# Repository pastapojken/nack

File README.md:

# nack
nack keyboard - uses [**QMK**](https://github.com/qmk/qmk_firmware)  
A ISO-friendly, 13x4 keyboard. It has hardware support for basically all the bells and whistles that qmk can provide!

You like my work? Feel free to donate :)  

")

")

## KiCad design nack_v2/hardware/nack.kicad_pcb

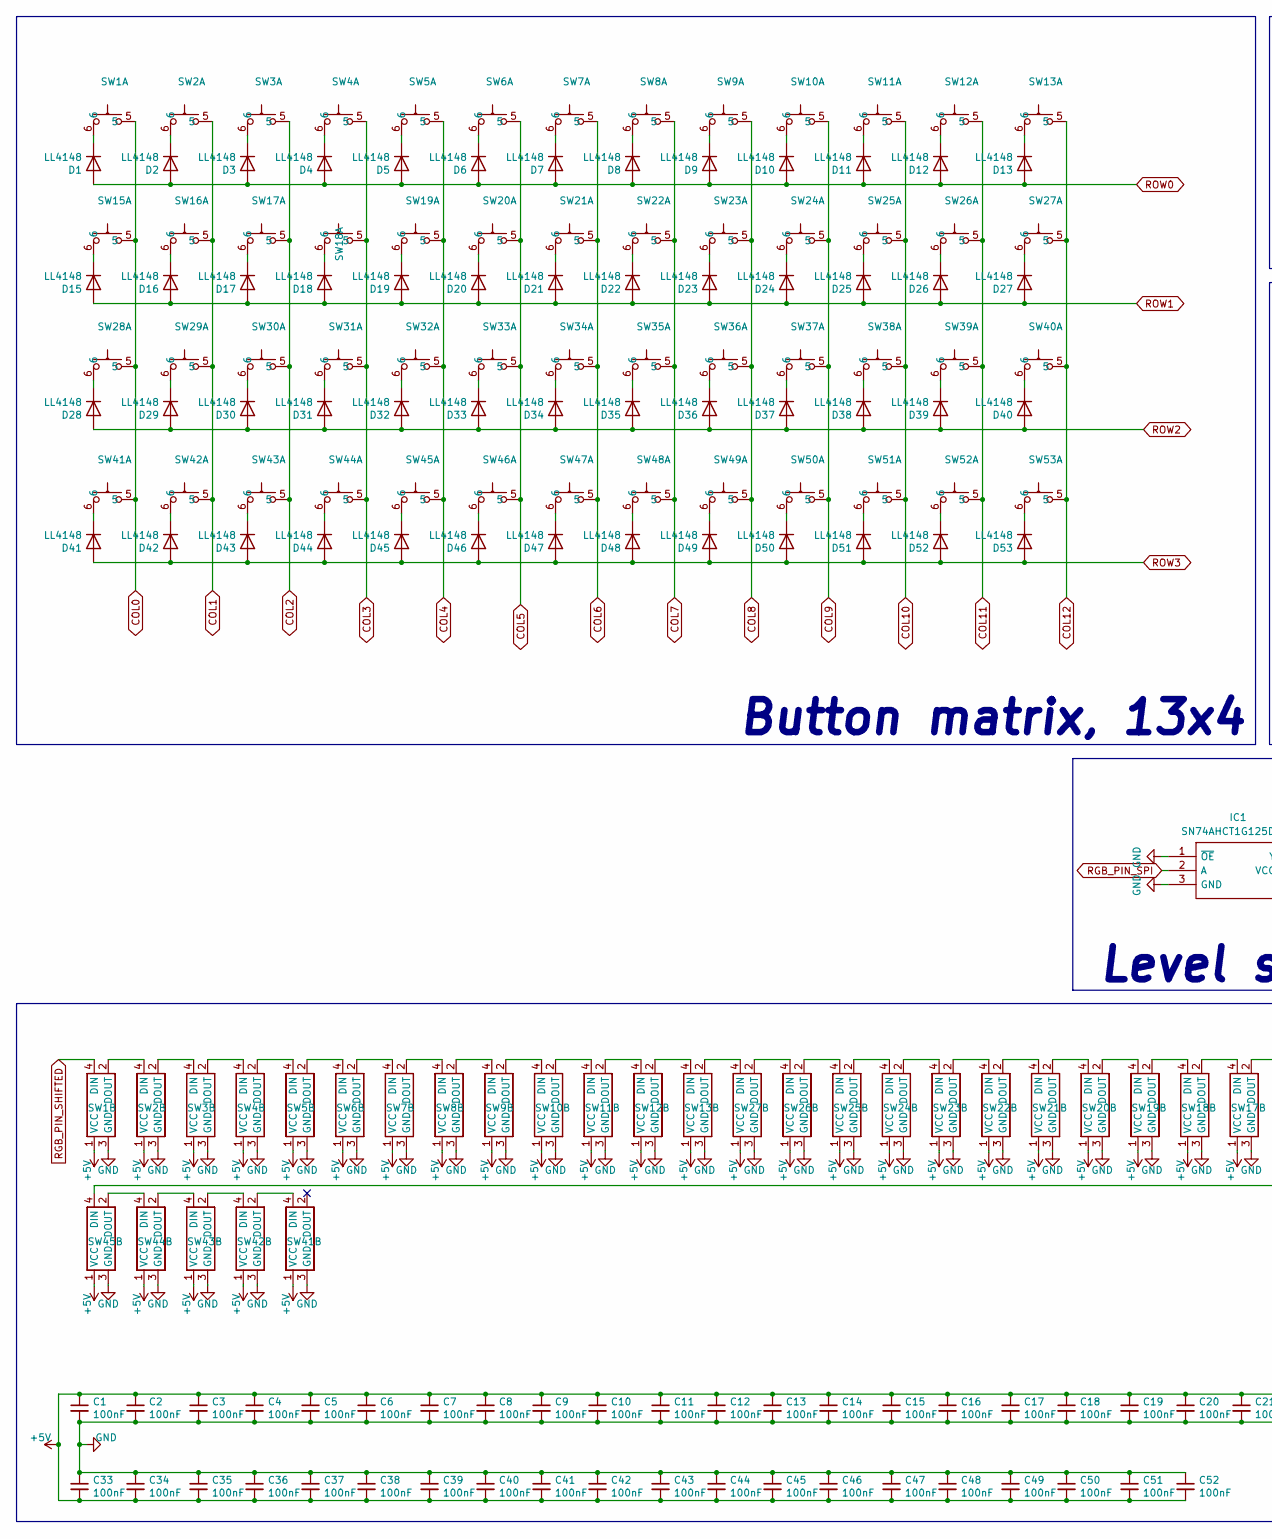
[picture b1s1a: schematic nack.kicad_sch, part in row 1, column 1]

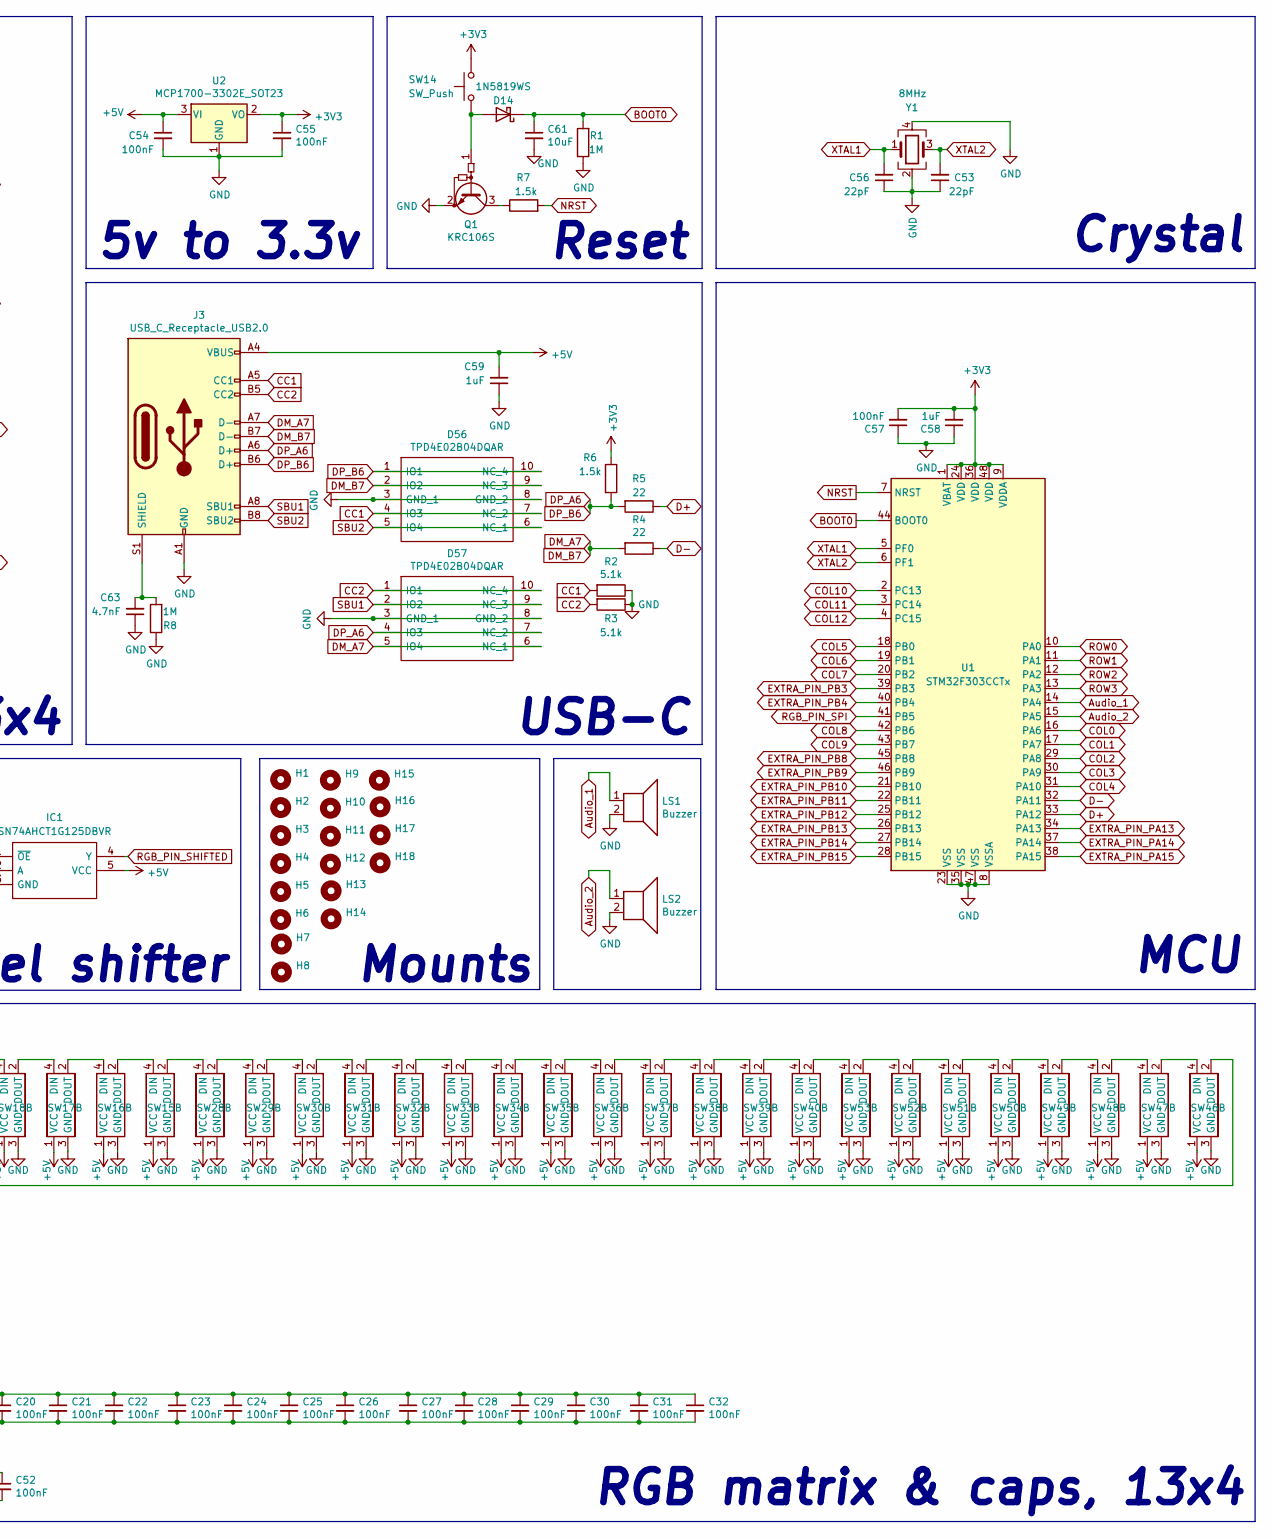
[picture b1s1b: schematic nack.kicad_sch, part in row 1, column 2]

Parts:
C1, C2, C3, C4, C5, C6, C7, C8, C9, C10, C11, C12, C13, C14, C15, C16, C17, C18, C19, C20, C21, C22, C23, C24, C25, C26, C27, C28, C29, C30, C31, C32, C33, C34, C35, C36, C37, C38, C39, C40, C41, C42, C43, C44, C45, C46, C47, C48, C49, C50, C51, C52, C54, C55, C57: 100nF; C_0402_1005Metric
C53, C56: 22pF; C_0402_1005Metric
C58, C59: 1uF; C_0402_1005Metric
C61: 10uF; C_0402_1005Metric
C63: 4.7nF; C_0402_1005Metric
D1, D2, D3, D4, D5, D6, D7, D8, D9, D10, D11, D12, D13, D15, D16, D17, D18, D19, D20, D21, D22, D23, D24, D25, D26, D27, D28, D29, D30, D31, D32, D33, D34, D35, D36, D37, D38, D39, D40, D41, D42, D43, D44, D45, D46, D47, D48, D49, D50, D51, D52, D53: LL4148; D_SOD-123
D14: 1N5819WS; D_SOD-323
D56, D57: TPD4E02B04DQAR; DQA(R-PUSON-N10); Manufacturer_Part_Number TPD4E02B04DQAR; Mouser Part Number 595-TPD4E02B04DQAR
H1, H2, H3, H4, H5, H6, H7, H8, H9, H10, H11, H12, H13, H14, H15, H16, H17, H18: MountingHole; MountingHole_M1.4
IC1: SN74AHCT1G125DBVR; SOT95P280X145-5N; Manufacturer_Part_Number SN74AHCT1G125DBVR; Mouser Part Number 595-SNAHCT1G125DBVR
J3: USB_C_Receptacle_USB2.0; USB_C_Receptacle
LS1, LS2: Buzzer; KLJ-1102
Q1: KRC106S; SOT-23
R1, R8: 1M; R_0402_1005Metric
R2, R3: 5.1k; R_0402_1005Metric
R4, R5: 22; R_0402_1005Metric
R6, R7: 1.5k; R_0402_1005Metric
SW1, SW2, SW3, SW4, SW5, SW6, SW7, SW8, SW9, SW10, SW11, SW12, SW13, SW28, SW29, SW30, SW31, SW32, SW33, SW34, SW35, SW36, SW37, SW38, SW39, SW40: SW_Hotswap_MX; SW_Cherry_MX_Hotswap_RevLED_flipped
SW14: SW_Push; SW_SPST_TL3342
SW15, SW16, SW17, SW18, SW19, SW20, SW21, SW22, SW23, SW24, SW25, SW26, SW27, SW41, SW42, SW43, SW44, SW45, SW46, SW47, SW48, SW49, SW50, SW51, SW52, SW53: SW_Hotswap_MX; SW_Cherry_MX_Hotswap_RevLED
U1: STM32F303CCTx; LQFP-48_7x7mm_P0.5mm; LCSC C81523
U2: MCP1700-3302E_SOT23; SOT-23
Y1: 8MHz; Crystal_SMD_3225-4Pin_3.2x2.5mm; LCSC C253751

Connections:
+3V3: C55.1, C57.2, C58.2, R6.1, SW14.2, U1.1 (VBAT), U1.9 (VDDA), U1.24 (VDD), U1.36 (VDD), U1.48 (VDD), U2.2 (VO)
+5V: C1.1, C2.1, C3.1, C4.1, C5.1, C6.1, C7.1, C8.1, C9.1, C10.1, C11.1, C12.1, C13.1, C14.1, C15.1, C16.1, C17.1, C18.1, C19.1, C20.1, C21.1, C22.1, C23.1, C24.1, C25.1, C26.1, C27.1, C28.1, C29.1, C30.1, C31.1, C32.1, C33.2, C34.2, C35.2, C36.2, C37.2, C38.2, C39.2, C40.2, C41.2, C42.2, C43.2, C44.2, C45.2, C46.2, C47.2, C48.2, C49.2, C50.2, C51.2, C52.2, C54.1, C59.2, IC1.5 (VCC), J3.A4 (VBUS), J3.A9 (VBUS), J3.B4 (VBUS), J3.B9 (VBUS), SW1.1 (VCC), SW2.1 (VCC), SW3.1 (VCC), SW4.1 (VCC), SW5.1 (VCC), SW6.1 (VCC), SW7.1 (VCC), SW8.1 (VCC), SW9.1 (VCC), SW10.1 (VCC), SW11.1 (VCC), SW12.1 (VCC), SW13.1 (VCC), SW15.1 (VCC), SW16.1 (VCC), SW17.1 (VCC), SW18.1 (VCC), SW19.1 (VCC), SW20.1 (VCC), SW21.1 (VCC), SW22.1 (VCC), SW23.1 (VCC), SW24.1 (VCC), SW25.1 (VCC), SW26.1 (VCC), SW27.1 (VCC), SW28.1 (VCC), SW29.1 (VCC), SW30.1 (VCC), SW31.1 (VCC), SW32.1 (VCC), SW33.1 (VCC), SW34.1 (VCC), SW35.1 (VCC), SW36.1 (VCC), SW37.1 (VCC), SW38.1 (VCC), SW39.1 (VCC), SW40.1 (VCC), SW41.1 (VCC), SW42.1 (VCC), SW43.1 (VCC), SW44.1 (VCC), SW45.1 (VCC), SW46.1 (VCC), SW47.1 (VCC), SW48.1 (VCC), SW49.1 (VCC), SW50.1 (VCC), SW51.1 (VCC), SW52.1 (VCC), SW53.1 (VCC), U2.3 (VI)
Audio_1: LS1.1, U1.14 (PA4)
Audio_2: LS2.1, U1.15 (PA5)
BOOT0: C61.1, D14.1 (K), R1.2, U1.44 (BOOT0)
CC1: D56.4 (IO3), D56.7 (NC_2), J3.A5 (CC1), R2.2
CC2: D57.1 (IO1), D57.10 (NC_4), J3.B5 (CC2), R3.2
COL0: SW1.5, SW15.5, SW28.5, SW41.5, U1.16 (PA6)
COL1: SW2.5, SW16.5, SW29.5, SW42.5, U1.17 (PA7)
COL2: SW3.5, SW17.5, SW30.5, SW43.5, U1.29 (PA8)
COL3: SW4.5, SW18.5, SW31.5, SW44.5, U1.30 (PA9)
COL4: SW5.5, SW19.5, SW32.5, SW45.5, U1.31 (PA10)
COL5: SW6.5, SW20.5, SW33.5, SW46.5, U1.18 (PB0)
COL6: SW7.5, SW21.5, SW34.5, SW47.5, U1.19 (PB1)
COL7: SW8.5, SW22.5, SW35.5, SW48.5, U1.20 (PB2)
COL8: SW9.5, SW23.5, SW36.5, SW49.5, U1.42 (PB6)
COL9: SW10.5, SW24.5, SW37.5, SW50.5, U1.43 (PB7)
COL10: SW11.5, SW25.5, SW38.5, SW51.5, U1.2 (PC13)
COL11: SW12.5, SW26.5, SW39.5, SW52.5, U1.3 (PC14)
COL12: SW13.5, SW27.5, SW40.5, SW53.5, U1.4 (PC15)
D+: R5.1, U1.33 (PA12)
D-: R4.1, U1.32 (PA11)
DM_A7: D56.2 (IO2), D56.9 (NC_3), D57.5 (IO4), D57.6 (NC_1), J3.A7 (D-), J3.B7 (D-), R4.2
DP_A6: D56.1 (IO1), D56.10 (NC_4), D57.4 (IO3), D57.7 (NC_2), J3.A6 (D+), J3.B6 (D+), R5.2, R6.2
EXTRA_PIN_PA13: U1.34 (PA13)
EXTRA_PIN_PA14: U1.37 (PA14)
EXTRA_PIN_PA15: U1.38 (PA15)
EXTRA_PIN_PB3: U1.39 (PB3)
EXTRA_PIN_PB4: U1.40 (PB4)
EXTRA_PIN_PB8: U1.45 (PB8)
EXTRA_PIN_PB9: U1.46 (PB9)
EXTRA_PIN_PB10: U1.21 (PB10)
EXTRA_PIN_PB11: U1.22 (PB11)
EXTRA_PIN_PB12: U1.25 (PB12)
EXTRA_PIN_PB13: U1.26 (PB13)
EXTRA_PIN_PB14: U1.27 (PB14)
EXTRA_PIN_PB15: U1.28 (PB15)
GND: C1.2, C2.2, C3.2, C4.2, C5.2, C6.2, C7.2, C8.2, C9.2, C10.2, C11.2, C12.2, C13.2, C14.2, C15.2, C16.2, C17.2, C18.2, C19.2, C20.2, C21.2, C22.2, C23.2, C24.2, C25.2, C26.2, C27.2, C28.2, C29.2, C30.2, C31.2, C32.2, C33.1, C34.1, C35.1, C36.1, C37.1, C38.1, C39.1, C40.1, C41.1, C42.1, C43.1, C44.1, C45.1, C46.1, C47.1, C48.1, C49.1, C50.1, C51.1, C52.1, C53.1, C54.2, C55.2, C56.1, C57.1, C58.1, C59.1, C61.2, C63.1, D56.3 (GND_1), D56.8 (GND_2), D57.3 (GND_1), D57.8 (GND_2), IC1.1 (~OE), IC1.3 (GND), J3.A1 (GND), J3.A12 (GND), J3.B1 (GND), J3.B12 (GND), LS1.2, LS2.2, Q1.2 (E), R1.1, R2.1, R3.1, R8.1, SW1.3 (GND), SW2.3 (GND), SW3.3 (GND), SW4.3 (GND), SW5.3 (GND), SW6.3 (GND), SW7.3 (GND), SW8.3 (GND), SW9.3 (GND), SW10.3 (GND), SW11.3 (GND), SW12.3 (GND), SW13.3 (GND), SW15.3 (GND), SW16.3 (GND), SW17.3 (GND), SW18.3 (GND), SW19.3 (GND), SW20.3 (GND), SW21.3 (GND), SW22.3 (GND), SW23.3 (GND), SW24.3 (GND), SW25.3 (GND), SW26.3 (GND), SW27.3 (GND), SW28.3 (GND), SW29.3 (GND), SW30.3 (GND), SW31.3 (GND), SW32.3 (GND), SW33.3 (GND), SW34.3 (GND), SW35.3 (GND), SW36.3 (GND), SW37.3 (GND), SW38.3 (GND), SW39.3 (GND), SW40.3 (GND), SW41.3 (GND), SW42.3 (GND), SW43.3 (GND), SW44.3 (GND), SW45.3 (GND), SW46.3 (GND), SW47.3 (GND), SW48.3 (GND), SW49.3 (GND), SW50.3 (GND), SW51.3 (GND), SW52.3 (GND), SW53.3 (GND), U1.8 (VSSA), U1.23 (VSS), U1.35 (VSS), U1.47 (VSS), U2.1 (GND), Y1.2, Y1.4
NRST: R7.2, U1.7 (NRST)
unnamed: D1.1 (K), SW1.6
unnamed: D2.1 (K), SW2.6
unnamed: D3.1 (K), SW3.6
unnamed: D4.1 (K), SW4.6
unnamed: D5.1 (K), SW5.6
unnamed: D6.1 (K), SW6.6
unnamed: D7.1 (K), SW7.6
unnamed: D8.1 (K), SW8.6
unnamed: D9.1 (K), SW9.6
unnamed: D10.1 (K), SW10.6
unnamed: D11.1 (K), SW11.6
unnamed: D12.1 (K), SW12.6
unnamed: D13.1 (K), SW13.6
unnamed: D14.2 (A), Q1.1 (B), SW14.1
unnamed: D15.1 (K), SW15.6
unnamed: D16.1 (K), SW16.6
unnamed: D17.1 (K), SW17.6
unnamed: D18.1 (K), SW18.6
unnamed: D19.1 (K), SW19.6
unnamed: D20.1 (K), SW20.6
unnamed: D21.1 (K), SW21.6
unnamed: D22.1 (K), SW22.6
unnamed: D23.1 (K), SW23.6
unnamed: D24.1 (K), SW24.6
unnamed: D25.1 (K), SW25.6
unnamed: D26.1 (K), SW26.6
unnamed: D27.1 (K), SW27.6
unnamed: D28.1 (K), SW28.6
unnamed: D29.1 (K), SW29.6
unnamed: D30.1 (K), SW30.6
unnamed: D31.1 (K), SW31.6
unnamed: D32.1 (K), SW32.6
unnamed: D33.1 (K), SW33.6
unnamed: D34.1 (K), SW34.6
unnamed: D35.1 (K), SW35.6
unnamed: D36.1 (K), SW36.6
unnamed: D37.1 (K), SW37.6
unnamed: D38.1 (K), SW38.6
unnamed: D39.1 (K), SW39.6
unnamed: D40.1 (K), SW40.6
unnamed: D41.1 (K), SW41.6
unnamed: D42.1 (K), SW42.6
unnamed: D43.1 (K), SW43.6
unnamed: D44.1 (K), SW44.6
unnamed: D45.1 (K), SW45.6
unnamed: D46.1 (K), SW46.6
unnamed: D47.1 (K), SW47.6
unnamed: D48.1 (K), SW48.6
unnamed: D49.1 (K), SW49.6
unnamed: D50.1 (K), SW50.6
unnamed: D51.1 (K), SW51.6
unnamed: D52.1 (K), SW52.6
unnamed: D53.1 (K), SW53.6
unnamed: C63.2, J3.S1 (SHIELD), R8.2
unnamed: Q1.3 (C), R7.1
unnamed: SW1.2 (DOUT), SW2.4 (DIN)
unnamed: SW2.2 (DOUT), SW3.4 (DIN)
unnamed: SW3.2 (DOUT), SW4.4 (DIN)
unnamed: SW4.2 (DOUT), SW5.4 (DIN)
unnamed: SW5.2 (DOUT), SW6.4 (DIN)
unnamed: SW6.2 (DOUT), SW7.4 (DIN)
unnamed: SW7.2 (DOUT), SW8.4 (DIN)
unnamed: SW8.2 (DOUT), SW9.4 (DIN)
unnamed: SW9.2 (DOUT), SW10.4 (DIN)
unnamed: SW10.2 (DOUT), SW11.4 (DIN)
unnamed: SW11.2 (DOUT), SW12.4 (DIN)
unnamed: SW12.2 (DOUT), SW13.4 (DIN)
unnamed: SW13.2 (DOUT), SW27.4 (DIN)
unnamed: SW15.4 (DIN), SW16.2 (DOUT)
unnamed: SW15.2 (DOUT), SW28.4 (DIN)
unnamed: SW16.4 (DIN), SW17.2 (DOUT)
unnamed: SW17.4 (DIN), SW18.2 (DOUT)
unnamed: SW18.4 (DIN), SW19.2 (DOUT)
unnamed: SW19.4 (DIN), SW20.2 (DOUT)
unnamed: SW20.4 (DIN), SW21.2 (DOUT)
unnamed: SW21.4 (DIN), SW22.2 (DOUT)
unnamed: SW22.4 (DIN), SW23.2 (DOUT)
unnamed: SW23.4 (DIN), SW24.2 (DOUT)
unnamed: SW24.4 (DIN), SW25.2 (DOUT)
unnamed: SW25.4 (DIN), SW26.2 (DOUT)
unnamed: SW26.4 (DIN), SW27.2 (DOUT)
unnamed: SW28.2 (DOUT), SW29.4 (DIN)
unnamed: SW29.2 (DOUT), SW30.4 (DIN)
unnamed: SW30.2 (DOUT), SW31.4 (DIN)
unnamed: SW31.2 (DOUT), SW32.4 (DIN)
unnamed: SW32.2 (DOUT), SW33.4 (DIN)
unnamed: SW33.2 (DOUT), SW34.4 (DIN)
unnamed: SW34.2 (DOUT), SW35.4 (DIN)
unnamed: SW35.2 (DOUT), SW36.4 (DIN)
unnamed: SW36.2 (DOUT), SW37.4 (DIN)
unnamed: SW37.2 (DOUT), SW38.4 (DIN)
unnamed: SW38.2 (DOUT), SW39.4 (DIN)
unnamed: SW39.2 (DOUT), SW40.4 (DIN)
unnamed: SW40.2 (DOUT), SW53.4 (DIN)
unnamed: SW41.4 (DIN), SW42.2 (DOUT)
unnamed: SW42.4 (DIN), SW43.2 (DOUT)
unnamed: SW43.4 (DIN), SW44.2 (DOUT)
unnamed: SW44.4 (DIN), SW45.2 (DOUT)
unnamed: SW45.4 (DIN), SW46.2 (DOUT)
unnamed: SW46.4 (DIN), SW47.2 (DOUT)
unnamed: SW47.4 (DIN), SW48.2 (DOUT)
unnamed: SW48.4 (DIN), SW49.2 (DOUT)
unnamed: SW49.4 (DIN), SW50.2 (DOUT)
unnamed: SW50.4 (DIN), SW51.2 (DOUT)
unnamed: SW51.4 (DIN), SW52.2 (DOUT)
unnamed: SW52.4 (DIN), SW53.2 (DOUT)
RGB_PIN_SHIFTED: IC1.4 (Y), SW1.4 (DIN)
RGB_PIN_SPI: IC1.2 (A), U1.41 (PB5)
ROW0: D1.2 (A), D2.2 (A), D3.2 (A), D4.2 (A), D5.2 (A), D6.2 (A), D7.2 (A), D8.2 (A), D9.2 (A), D10.2 (A), D11.2 (A), D12.2 (A), D13.2 (A), U1.10 (PA0)
ROW1: D15.2 (A), D16.2 (A), D17.2 (A), D18.2 (A), D19.2 (A), D20.2 (A), D21.2 (A), D22.2 (A), D23.2 (A), D24.2 (A), D25.2 (A), D26.2 (A), D27.2 (A), U1.11 (PA1)
ROW2: D28.2 (A), D29.2 (A), D30.2 (A), D31.2 (A), D32.2 (A), D33.2 (A), D34.2 (A), D35.2 (A), D36.2 (A), D37.2 (A), D38.2 (A), D39.2 (A), D40.2 (A), U1.12 (PA2)
ROW3: D41.2 (A), D42.2 (A), D43.2 (A), D44.2 (A), D45.2 (A), D46.2 (A), D47.2 (A), D48.2 (A), D49.2 (A), D50.2 (A), D51.2 (A), D52.2 (A), D53.2 (A), U1.13 (PA3)
SBU1: D57.2 (IO2), D57.9 (NC_3), J3.A8 (SBU1)
SBU2: D56.5 (IO4), D56.6 (NC_1), J3.B8 (SBU2)
XTAL1: C56.2, U1.5 (PF0), Y1.1
XTAL2: C53.2, U1.6 (PF1), Y1.3

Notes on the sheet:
Mounts
USB-C
Crystal
RGB matrix & caps, 13x4
Reset
Button matrix, 13x4
5v to 3.3v
Level shifter
MCU

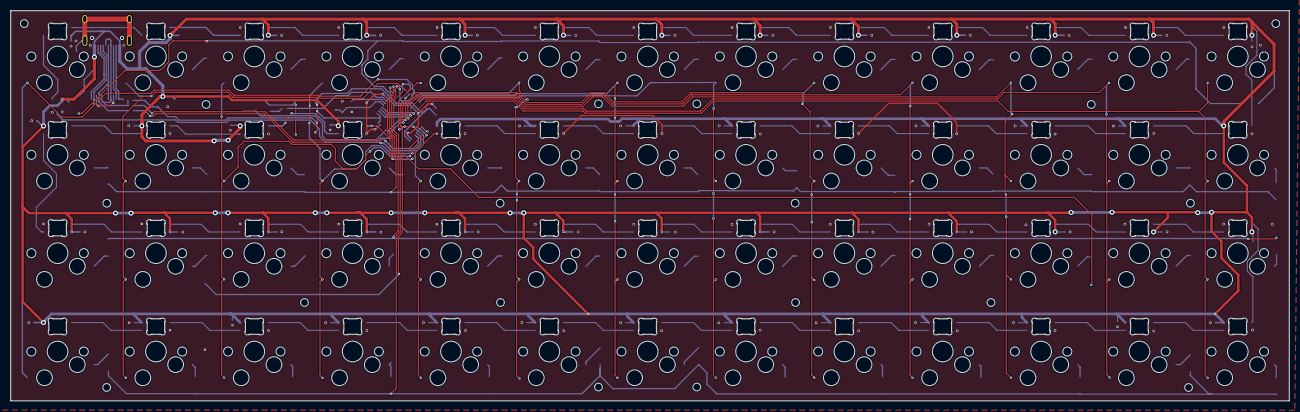
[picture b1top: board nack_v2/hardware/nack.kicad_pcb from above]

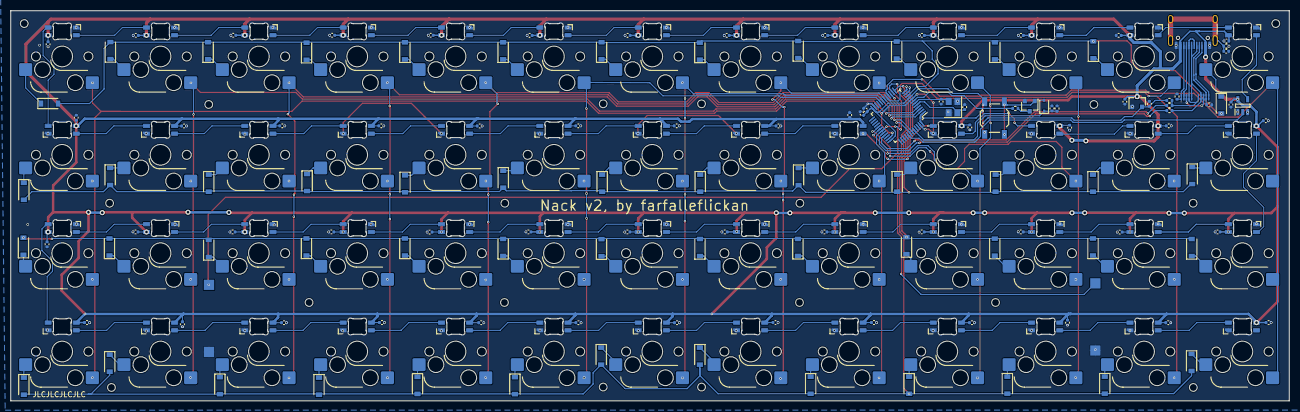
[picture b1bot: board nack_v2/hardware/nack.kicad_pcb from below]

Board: 2 copper layers, 247.6 x 75.6 mm, 203 parts (133 on the bottom side), 142 nets.

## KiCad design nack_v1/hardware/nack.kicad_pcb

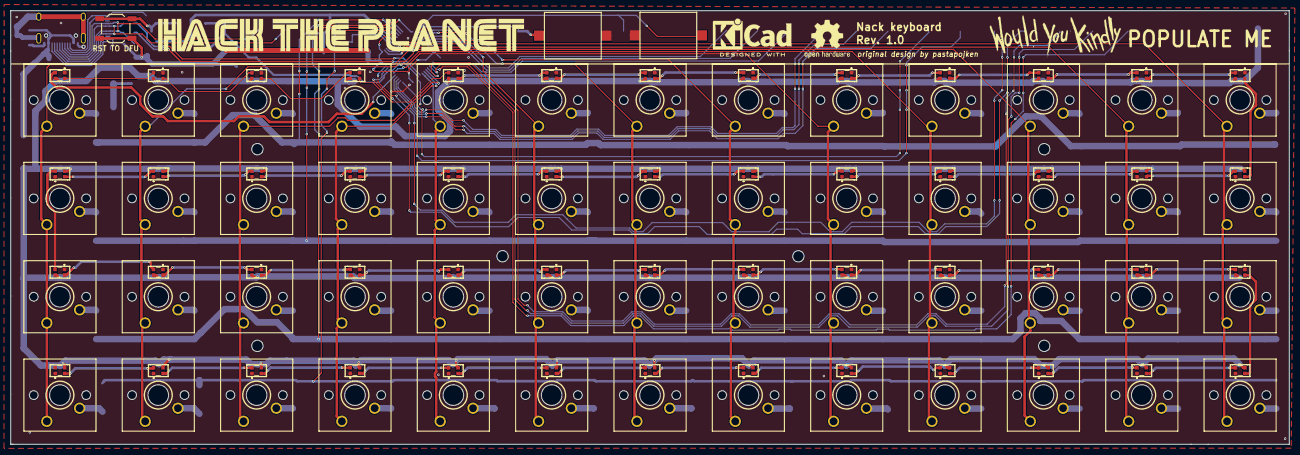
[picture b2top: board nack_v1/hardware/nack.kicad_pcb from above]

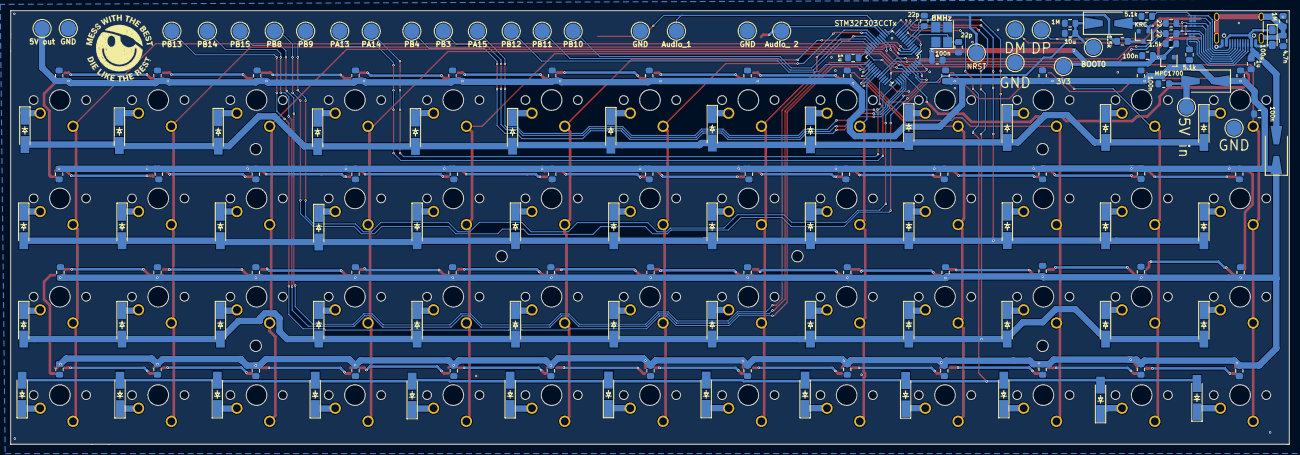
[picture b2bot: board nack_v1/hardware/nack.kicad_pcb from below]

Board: 2 copper layers, 247.7 x 84.0 mm, 273 parts (160 on the bottom side), 156 nets.

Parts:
C1, C2, C3, C4, C5, C6, C7, C8, C9, C10, C11, C12, C13, C14, C15, C16, C17, C18, C19, C20, C21, C22, C23, C24, C25, C26, C27, C28, C29, C30, C31, C32, C33, C34, C35, C36, C37, C38, C39, C40, C41, C42, C43, C44, C45, C46, C47, C48, C49, C50, C51, C52, C54, C55, C57, C60: 100nF; C_0805_2012Metric_Pad1.15x1.40mm_HandSolder
C53, C56: 22pF; C_0805_2012Metric_Pad1.15x1.40mm_HandSolder
C58, C59: 1uF; C_0805_2012Metric_Pad1.15x1.40mm_HandSolder
C61: 10uF; C_0805_2012Metric_Pad1.15x1.40mm_HandSolder
C62: 100uF; CP_EIA-3216-18_Kemet-A_Pad1.58x1.35mm_HandSolder
C63: 4.7nF; C_0805_2012Metric_Pad1.15x1.40mm_HandSolder
D1, D2, D3, D4, D5, D6, D7, D8, D9, D10, D11, D12, D13, D15, D16, D17, D18, D19, D20, D21, D22, D23, D24, D25, D26, D27, D28, D29, D30, D31, D32, D33, D34, D35, D36, D37, D38, D39, D40, D41, D42, D43, D44, D45, D46, D47, D48, D49, D50, D51, D52, D53: LL4148; D_MiniMELF_Handsoldering
D14, D54, D55: Diode; D_SMA-SMB_Universal_Handsoldering
D56, D57: TPD4E02B04DQAR; DQA(R-PUSON-N10)
H1, H2, H3, H4, H5, H6: MountingHole; MountingHole_2.2mm_M2
J1: 5V in; TestPoint_Pad_D3.0mm
J2: 5V out; TestPoint_Pad_D3.0mm
J3: USB_C_Receptacle_USB2.0; USB_C_Receptacle
J4, J5, J6, J7, J8, J9, J10, J11, J12, J13, J14, J15, J16, J17, J18, J19, J20, J21, J22, J23, J24, J25: Conn_01x01_Female; TestPoint_Pad_D3.0mm
J26: NRST; TestPoint_Pad_D3.0mm
J27: BOOT0; TestPoint_Pad_D3.0mm
J28: 3V3; TestPoint_Pad_D3.0mm
LED1, LED2, LED3, LED4, LED5, LED6, LED7, LED8, LED9, LED10, LED11, LED12, LED13, LED14, LED15, LED16, LED17, LED18, LED19, LED20, LED21, LED22, LED23, LED24, LED25, LED26, LED27, LED28, LED29, LED30, LED31, LED32, LED33, LED34, LED35, LED36, LED37, LED38, LED39, LED40, LED41, LED42, LED43, LED44, LED45, LED46, LED47, LED48, LED49, LED50, LED51, LED52: WS2812C-2020; WS2812C2020
LS1, LS2: Buzzer; KLJ-1102
Q1: KRC106S; SOT-23
R1, R8: 1M; R_0805_2012Metric_Pad1.15x1.40mm_HandSolder
R2, R3: 5.1k; R_0805_2012Metric_Pad1.15x1.40mm_HandSolder
R4, R5: 22; R_0805_2012Metric_Pad1.15x1.40mm_HandSolder
R6, R7: 1.5k; R_0805_2012Metric_Pad1.15x1.40mm_HandSolder
SW1, SW2, SW3, SW4, SW5, SW6, SW7, SW8, SW9, SW10, SW11, SW12, SW13, SW15, SW16, SW17, SW18, SW19, SW20, SW21, SW22, SW23, SW24, SW25, SW26, SW27, SW28, SW29, SW30, SW31, SW32, SW33, SW34, SW35, SW36, SW37, SW38, SW39, SW40, SW41, SW42, SW43, SW44, SW45, SW46, SW47, SW48, SW49, SW50, SW51, SW52, SW53: SW_Push_90; SW_Cherry_MX_1.00u_Plate_LED_Guide
SW14: SW_Push; SW_SPST_TL3342
U1: STM32F303CCTx; LQFP-48_7x7mm_P0.5mm
U2: MCP1700-3302E_SOT23; SOT-23
Y1: 8MHz; Crystal_SMD_3225-4Pin_3.2x2.5mm_HandSoldering

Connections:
+3V3: C55.1, C57.2, C58.2, J28.1, R6.1, SW14.2, U1.1, U1.9, U1.24, U1.36, U1.48, U2.2
+5V: C1.1, C2.1, C3.1, C4.1, C5.1, C6.1, C7.1, C8.1, C9.1, C10.1, C11.1, C12.1, C13.1, C14.1, C15.1, C16.1, C17.1, C18.1, C19.1, C20.1, C21.1, C22.1, C23.1, C24.1, C25.1, C26.1, C27.1, C28.1, C29.1, C30.1, C31.1, C32.1, C33.2, C34.2, C35.2, C36.2, C37.2, C38.2, C39.2, C40.2, C41.2, C42.2, C43.2, C44.2, C45.2, C46.2, C47.2, C48.2, C49.2, C50.2, C51.2, C52.2, C54.1, D54.1, D55.1, J2.1, LED1.4, LED2.4, LED3.4, LED4.4, LED5.4, LED6.4, LED7.4, LED8.4, LED9.4, LED10.4, LED11.4, LED12.4, LED13.4, LED14.4, LED15.4, LED16.4, LED17.4, LED18.4, LED19.4, LED20.4, LED21.4, LED22.4, LED23.4, LED24.4, LED25.4, LED26.4, LED27.4, LED28.4, LED29.4, LED30.4, LED31.4, LED32.4, LED33.4, LED34.4, LED35.4, LED36.4, LED37.4, LED38.4, LED39.4, LED40.4, LED41.4, LED42.4, LED43.4, LED44.4, LED45.4, LED46.4, LED47.4, LED48.4, LED49.4, LED50.4, LED51.4, LED52.4, U2.3
Audio_1: J4.1, LS1.1, U1.14
Audio_2: J12.1, LS2.1, U1.15
BOOT0: C61.1, D14.1, J27.1, R1.2, U1.44
CC1: D56.4, D56.7, J3.A5, R2.2
CC2: D57.1, D57.10, J3.B5, R3.2
COL0: SW1.2, SW15.2, SW28.2, SW41.2, U1.16
COL1: SW2.2, SW16.2, SW29.2, SW42.2, U1.17
COL2: SW3.2, SW17.2, SW30.2, SW43.2, U1.29
COL3: SW4.2, SW18.2, SW31.2, SW44.2, U1.30
COL4: SW5.2, SW19.2, SW32.2, SW45.2, U1.31
COL5: SW6.2, SW20.2, SW33.2, SW46.2, U1.18
COL6: SW7.2, SW21.2, SW34.2, SW47.2, U1.19
COL7: SW8.2, SW22.2, SW35.2, SW48.2, U1.20
COL8: SW9.2, SW23.2, SW36.2, SW49.2, U1.42
COL9: SW10.2, SW24.2, SW37.2, SW50.2, U1.43
COL10: SW11.2, SW25.2, SW38.2, SW51.2, U1.2
COL11: SW12.2, SW26.2, SW39.2, SW52.2, U1.3
COL12: SW13.2, SW27.2, SW40.2, SW53.2, U1.4
D+: R5.1, U1.33
D-: R4.1, U1.32
DM_A7: D56.2, D56.9, D57.5, D57.6, J3.A7, J3.B7, J24.1, R4.2
DP_A6: D56.1, D56.10, D57.4, D57.7, J3.A6, J3.B6, J23.1, R5.2, R6.2
EXTRA_PIN_PA13: J16.1, U1.34
EXTRA_PIN_PA14: J17.1, U1.37
EXTRA_PIN_PA15: J18.1, U1.38
EXTRA_PIN_PB3: J5.1, U1.39
EXTRA_PIN_PB4: J6.1, U1.40
EXTRA_PIN_PB8: J7.1, U1.45
EXTRA_PIN_PB9: J8.1, U1.46
EXTRA_PIN_PB10: J9.1, U1.21
EXTRA_PIN_PB11: J10.1, U1.22
EXTRA_PIN_PB12: J11.1, U1.25
EXTRA_PIN_PB13: J13.1, U1.26
EXTRA_PIN_PB14: J14.1, U1.27
EXTRA_PIN_PB15: J15.1, U1.28
GND: C1.2, C2.2, C3.2, C4.2, C5.2, C6.2, C7.2, C8.2, C9.2, C10.2, C11.2, C12.2, C13.2, C14.2, C15.2, C16.2, C17.2, C18.2, C19.2, C20.2, C21.2, C22.2, C23.2, C24.2, C25.2, C26.2, C27.2, C28.2, C29.2, C30.2, C31.2, C32.2, C33.1, C34.1, C35.1, C36.1, C37.1, C38.1, C39.1, C40.1, C41.1, C42.1, C43.1, C44.1, C45.1, C46.1, C47.1, C48.1, C49.1, C50.1, C51.1, C52.1, C53.1, C54.2, C55.2, C56.1, C57.1, C58.1, C59.1, C60.2, C61.2, C62.2, C63.1, D56.3, D56.8, D57.3, D57.8, J3.A1, J3.A12, J3.B1, J3.B12, J19.1, J20.1, J21.1, J22.1, J25.1, LED1.2, LED2.2, LED3.2, LED4.2, LED5.2, LED6.2, LED7.2, LED8.2, LED9.2, LED10.2, LED11.2, LED12.2, LED13.2, LED14.2, LED15.2, LED16.2, LED17.2, LED18.2, LED19.2, LED20.2, LED21.2, LED22.2, LED23.2, LED24.2, LED25.2, LED26.2, LED27.2, LED28.2, LED29.2, LED30.2, LED31.2, LED32.2, LED33.2, LED34.2, LED35.2, LED36.2, LED37.2, LED38.2, LED39.2, LED40.2, LED41.2, LED42.2, LED43.2, LED44.2, LED45.2, LED46.2, LED47.2, LED48.2, LED49.2, LED50.2, LED51.2, LED52.2, LS1.2, LS2.2, Q1.2, R1.1, R2.1, R3.1, R8.1, U1.8, U1.23, U1.35, U1.47, U2.1, Y1.2, Y1.4
NRST: J26.1, R7.2, U1.7
unnamed: C59.2, C62.1, D55.2, J3.A4, J3.A9, J3.B4, J3.B9
unnamed: C60.1, D54.2, J1.1
unnamed: C63.2, J3.S1, R8.2
unnamed: D1.2, SW1.1
unnamed: D2.2, SW2.1
unnamed: D3.2, SW3.1
unnamed: D4.2, SW4.1
unnamed: D5.2, SW5.1
unnamed: D6.2, SW6.1
unnamed: D7.2, SW7.1
unnamed: D8.2, SW8.1
unnamed: D9.2, SW9.1
unnamed: D10.2, SW10.1
unnamed: D11.2, SW11.1
unnamed: D12.2, SW12.1
unnamed: D13.2, SW13.1
unnamed: D14.2, Q1.1, SW14.1
unnamed: D15.2, SW15.1
unnamed: D16.2, SW16.1
unnamed: D17.2, SW17.1
unnamed: D18.2, SW18.1
unnamed: D19.2, SW19.1
unnamed: D20.2, SW20.1
unnamed: D21.2, SW21.1
unnamed: D22.2, SW22.1
unnamed: D23.2, SW23.1
unnamed: D24.2, SW24.1
unnamed: D25.2, SW25.1
unnamed: D26.2, SW26.1
unnamed: D27.2, SW27.1
unnamed: D28.2, SW28.1
unnamed: D29.2, SW29.1
unnamed: D30.2, SW30.1
unnamed: D31.2, SW31.1
unnamed: D32.2, SW32.1
unnamed: D33.2, SW33.1
unnamed: D34.2, SW34.1
unnamed: D35.2, SW35.1
unnamed: D36.2, SW36.1
unnamed: D37.2, SW37.1
unnamed: D38.2, SW38.1
unnamed: D39.2, SW39.1
unnamed: D40.2, SW40.1
unnamed: D41.2, SW41.1
unnamed: D42.2, SW42.1
unnamed: D43.2, SW43.1
unnamed: D44.2, SW44.1
unnamed: D45.2, SW45.1
unnamed: D46.2, SW46.1
unnamed: D47.2, SW47.1
unnamed: D48.2, SW48.1
unnamed: D49.2, SW49.1
unnamed: D50.2, SW50.1
unnamed: D51.2, SW51.1
unnamed: D52.2, SW52.1
unnamed: D53.2, SW53.1
unnamed: LED1.1, LED2.3
unnamed: LED2.1, LED3.3
unnamed: LED3.1, LED4.3
unnamed: LED4.1, LED5.3
unnamed: LED5.1, LED6.3
unnamed: LED6.1, LED7.3
unnamed: LED7.1, LED8.3
unnamed: LED8.1, LED9.3
unnamed: LED10.1, LED11.3
unnamed: LED9.1, LED10.3
unnamed: LED11.1, LED12.3
unnamed: LED12.1, LED13.3
unnamed: LED13.1, LED14.3
unnamed: LED14.1, LED15.3
unnamed: LED15.1, LED16.3
unnamed: LED16.1, LED17.3
unnamed: LED17.1, LED18.3
unnamed: LED18.1, LED19.3
unnamed: LED19.1, LED20.3
unnamed: LED20.1, LED21.3
unnamed: LED21.1, LED22.3
unnamed: LED22.1, LED23.3
unnamed: LED23.1, LED24.3
unnamed: LED24.1, LED25.3
unnamed: LED25.1, LED26.3
unnamed: LED26.1, LED27.3
unnamed: LED27.1, LED28.3
unnamed: LED28.1, LED29.3
unnamed: LED29.1, LED30.3
unnamed: LED30.1, LED31.3
unnamed: LED31.1, LED32.3
unnamed: LED32.1, LED33.3
unnamed: LED33.1, LED34.3
unnamed: LED34.1, LED35.3
unnamed: LED35.1, LED36.3
unnamed: LED36.1, LED37.3
unnamed: LED37.1, LED38.3
unnamed: LED38.1, LED39.3
unnamed: LED39.1, LED40.3
unnamed: LED40.1, LED41.3
unnamed: LED41.1, LED42.3
unnamed: LED42.1, LED43.3
unnamed: LED43.1, LED44.3
unnamed: LED44.1, LED45.3
unnamed: LED45.1, LED46.3
unnamed: LED46.1, LED47.3
unnamed: LED47.1, LED48.3
unnamed: LED48.1, LED49.3
unnamed: LED49.1, LED50.3
unnamed: LED50.1, LED51.3
unnamed: LED51.1, LED52.3
unnamed: Q1.3, R7.1
RGB_PIN_SPI: LED1.3, U1.41
ROW0: D1.1, D2.1, D3.1, D4.1, D5.1, D6.1, D7.1, D8.1, D9.1, D10.1, D11.1, D12.1, D13.1, U1.10
ROW1: D15.1, D16.1, D17.1, D18.1, D19.1, D20.1, D21.1, D22.1, D23.1, D24.1, D25.1, D26.1, D27.1, U1.11
ROW2: D28.1, D29.1, D30.1, D31.1, D32.1, D33.1, D34.1, D35.1, D36.1, D37.1, D38.1, D39.1, D40.1, U1.12
ROW3: D41.1, D42.1, D43.1, D44.1, D45.1, D46.1, D47.1, D48.1, D49.1, D50.1, D51.1, D52.1, D53.1, U1.13
SBU1: D57.2, D57.9, J3.A8
SBU2: D56.5, D56.6, J3.B8
XTAL1: C56.2, U1.5, Y1.1
XTAL2: C53.2, U1.6, Y1.3

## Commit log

2024-03-15 New v2!
